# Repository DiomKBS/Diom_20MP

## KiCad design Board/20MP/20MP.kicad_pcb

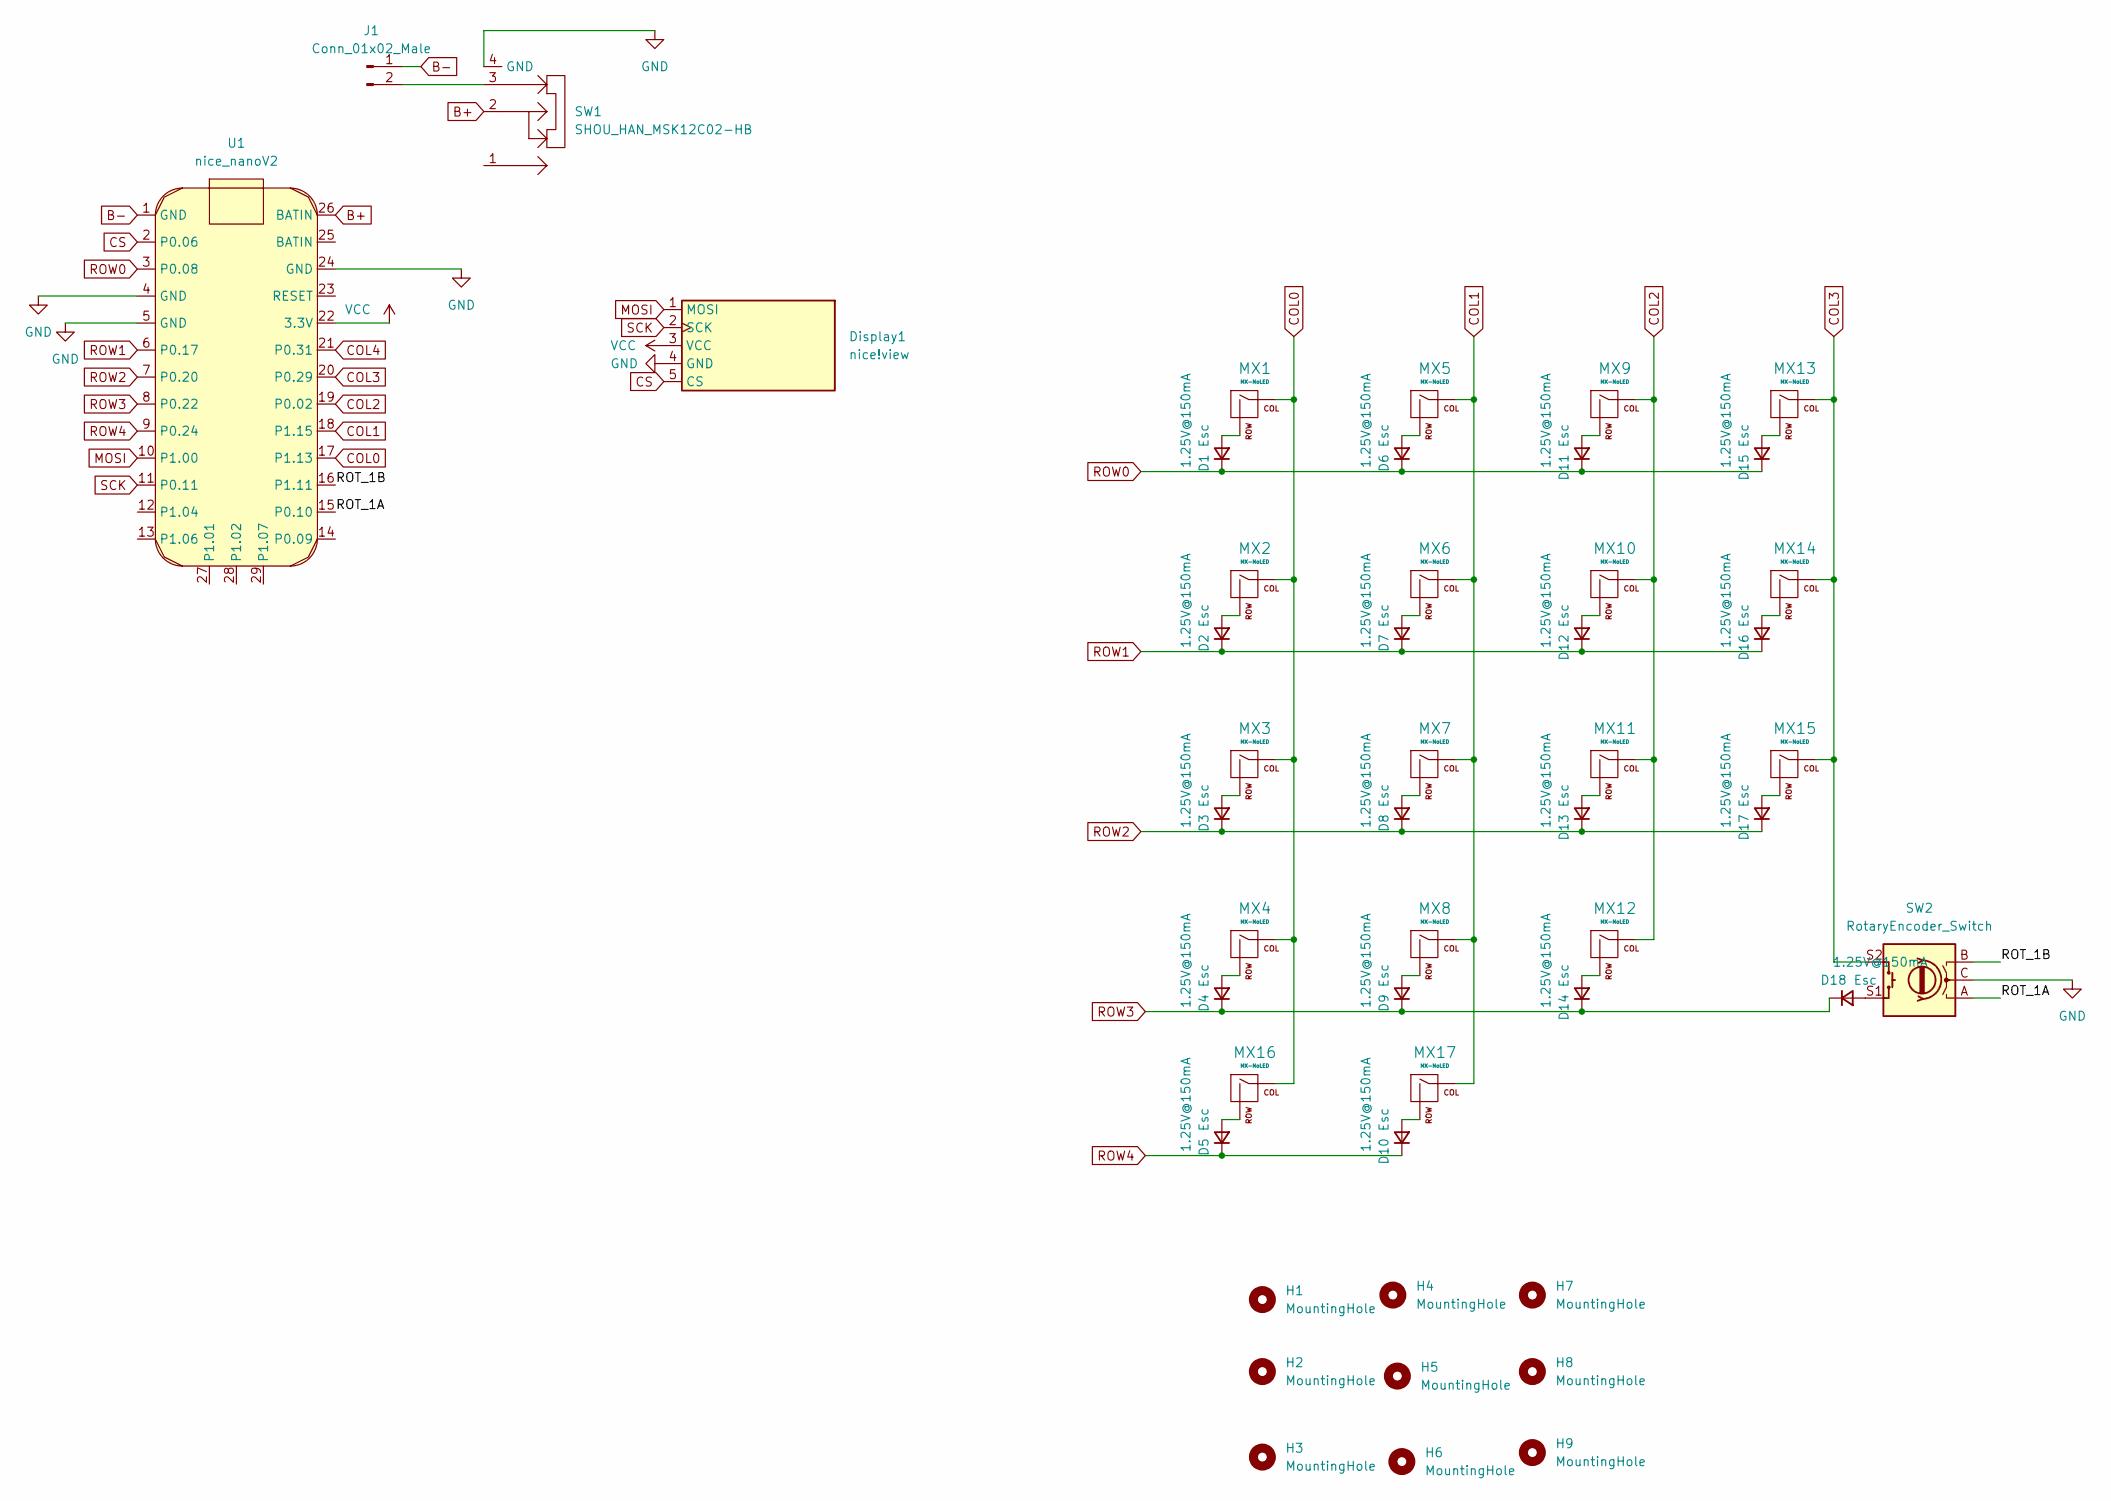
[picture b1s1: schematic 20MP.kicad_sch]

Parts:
D1, D2, D3, D4, D5, D6, D7, D8, D9, D10, D11, D12, D13, D14, D15, D16, D17, D18: 1.25V@150mA; D_SOD-123
Display1: nice!view; nice_view
H1, H2, H3, H4, H5, H6, H7, H8, H9: MountingHole; MountingHole_2.2mm_M2
J1: Conn_01x02_Male; THT_Battery
MX1, MX2, MX3, MX4, MX5, MX6, MX7, MX8, MX9, MX10, MX11, MX12, MX13, MX17: MX-NoLED; CherryMX-1.00U
MX14, MX15: MX-NoLED; CherryMX-2.00U_90deg
MX16: MX-NoLED; CherryMX-2.00U
SW1: SHOU_HAN_MSK12C02-HB; SHOU HAN MSK12C02-HB
SW2: RotaryEncoder_Switch; RotaryEncoder_EC11E-Switch
U1: nice_nanoV2

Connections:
/ROT_1A: SW2.A, U1.15 (P0.10)
/ROT_1B: SW2.B, U1.16 (P1.11)
B+: SW1.2, U1.26 (BATIN)
B-: J1.1, U1.1 (GND)
COL0: MX1.1 (COL), MX2.1 (COL), MX3.1 (COL), MX4.1 (COL), MX16.1 (COL), U1.17 (P1.13)
COL1: MX5.1 (COL), MX6.1 (COL), MX7.1 (COL), MX8.1 (COL), MX17.1 (COL), U1.18 (P1.15)
COL4: U1.21 (P0.31)
CS: Display1.5 (CS), U1.2 (P0.06)
GND: Display1.4 (GND), SW1.4 (GND), SW2.C, U1.4 (GND), U1.5 (GND), U1.24 (GND)
MOSI: Display1.1 (MOSI), U1.10 (P1.00)
unnamed: D1.2 (A), MX1.2 (ROW)
unnamed: D2.2 (A), MX2.2 (ROW)
unnamed: D3.2 (A), MX3.2 (ROW)
unnamed: D4.2 (A), MX4.2 (ROW)
unnamed: D5.2 (A), MX16.2 (ROW)
unnamed: D6.2 (A), MX5.2 (ROW)
unnamed: D7.2 (A), MX6.2 (ROW)
unnamed: D8.2 (A), MX7.2 (ROW)
unnamed: D9.2 (A), MX8.2 (ROW)
unnamed: D10.2 (A), MX17.2 (ROW)
unnamed: D11.2 (A), MX9.2 (ROW)
unnamed: D12.2 (A), MX10.2 (ROW)
unnamed: D13.2 (A), MX11.2 (ROW)
unnamed: D14.2 (A), MX12.2 (ROW)
unnamed: D15.2 (A), MX13.2 (ROW)
unnamed: D16.2 (A), MX14.2 (ROW)
unnamed: D17.2 (A), MX15.2 (ROW)
unnamed: D18.2 (A), SW2.S1
unnamed: J1.2, SW1.3
ROW0: D1.1 (K), D6.1 (K), D11.1 (K), D15.1 (K), U1.3 (P0.08)
ROW1: D2.1 (K), D7.1 (K), D12.1 (K), D16.1 (K), U1.6 (P0.17)
ROW2: D3.1 (K), D8.1 (K), D13.1 (K), D17.1 (K), U1.7 (P0.20)
ROW3: D4.1 (K), D9.1 (K), D14.1 (K), D18.1 (K), U1.8 (P0.22)
ROW4: D5.1 (K), D10.1 (K), U1.9 (P0.24)
SCK: Display1.2 (SCK), U1.11 (P0.11)
VCC: Display1.3 (VCC), U1.22 (3.3V)

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
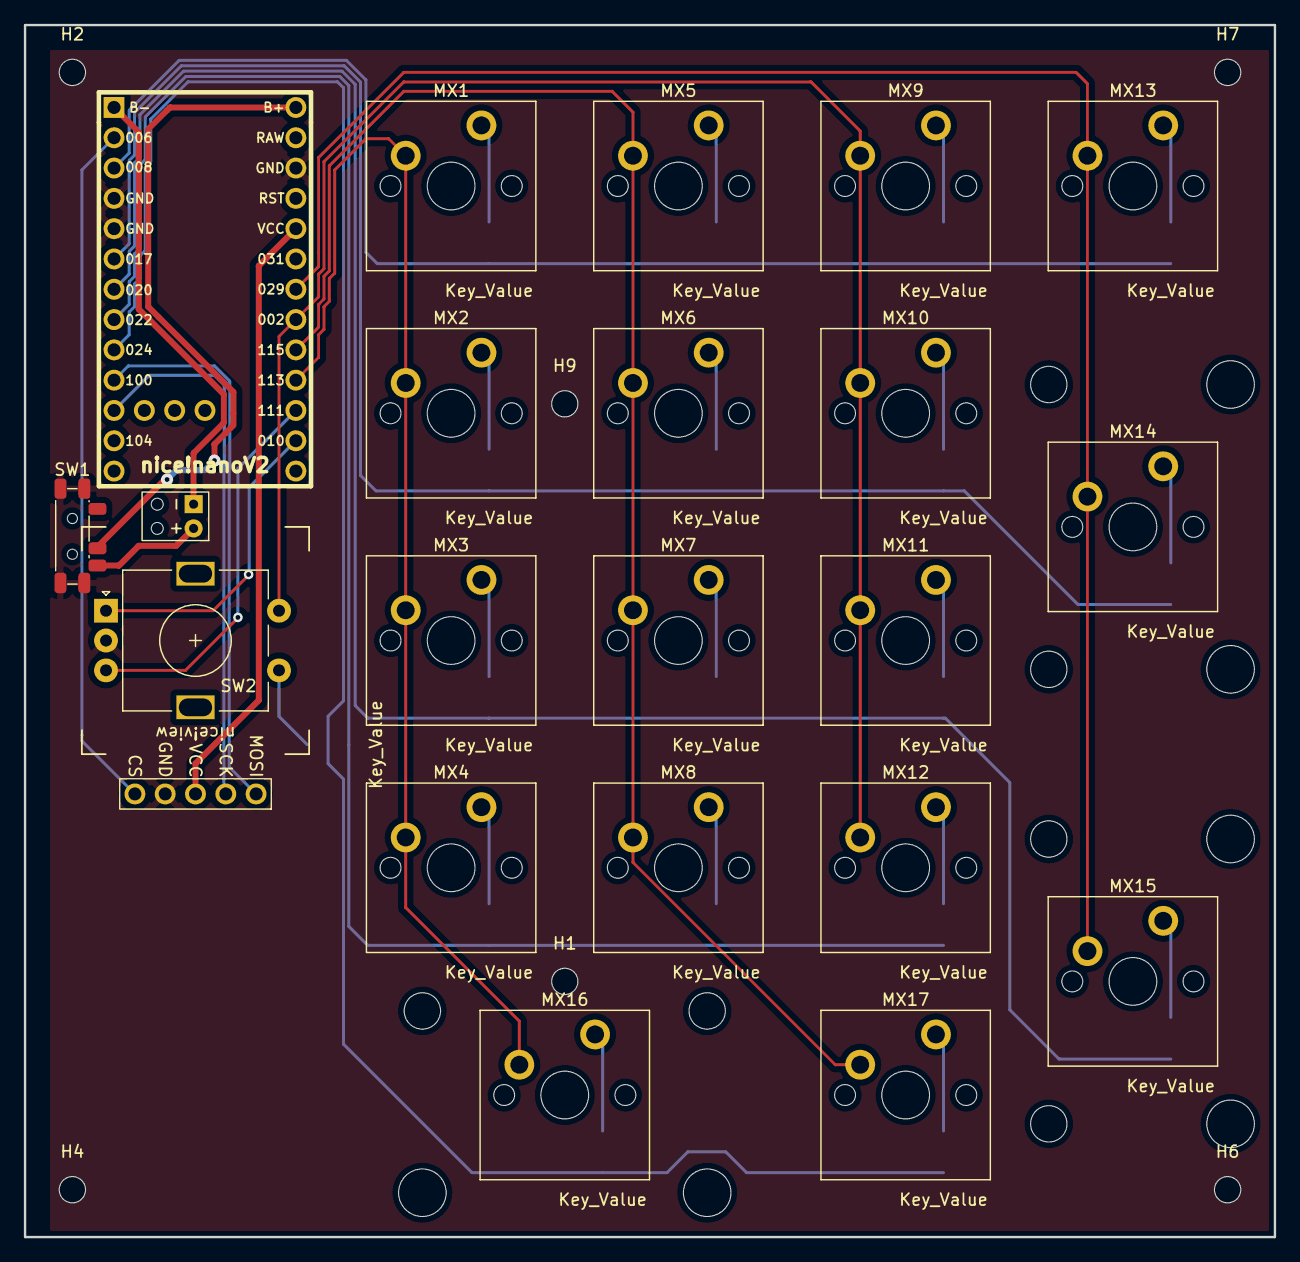
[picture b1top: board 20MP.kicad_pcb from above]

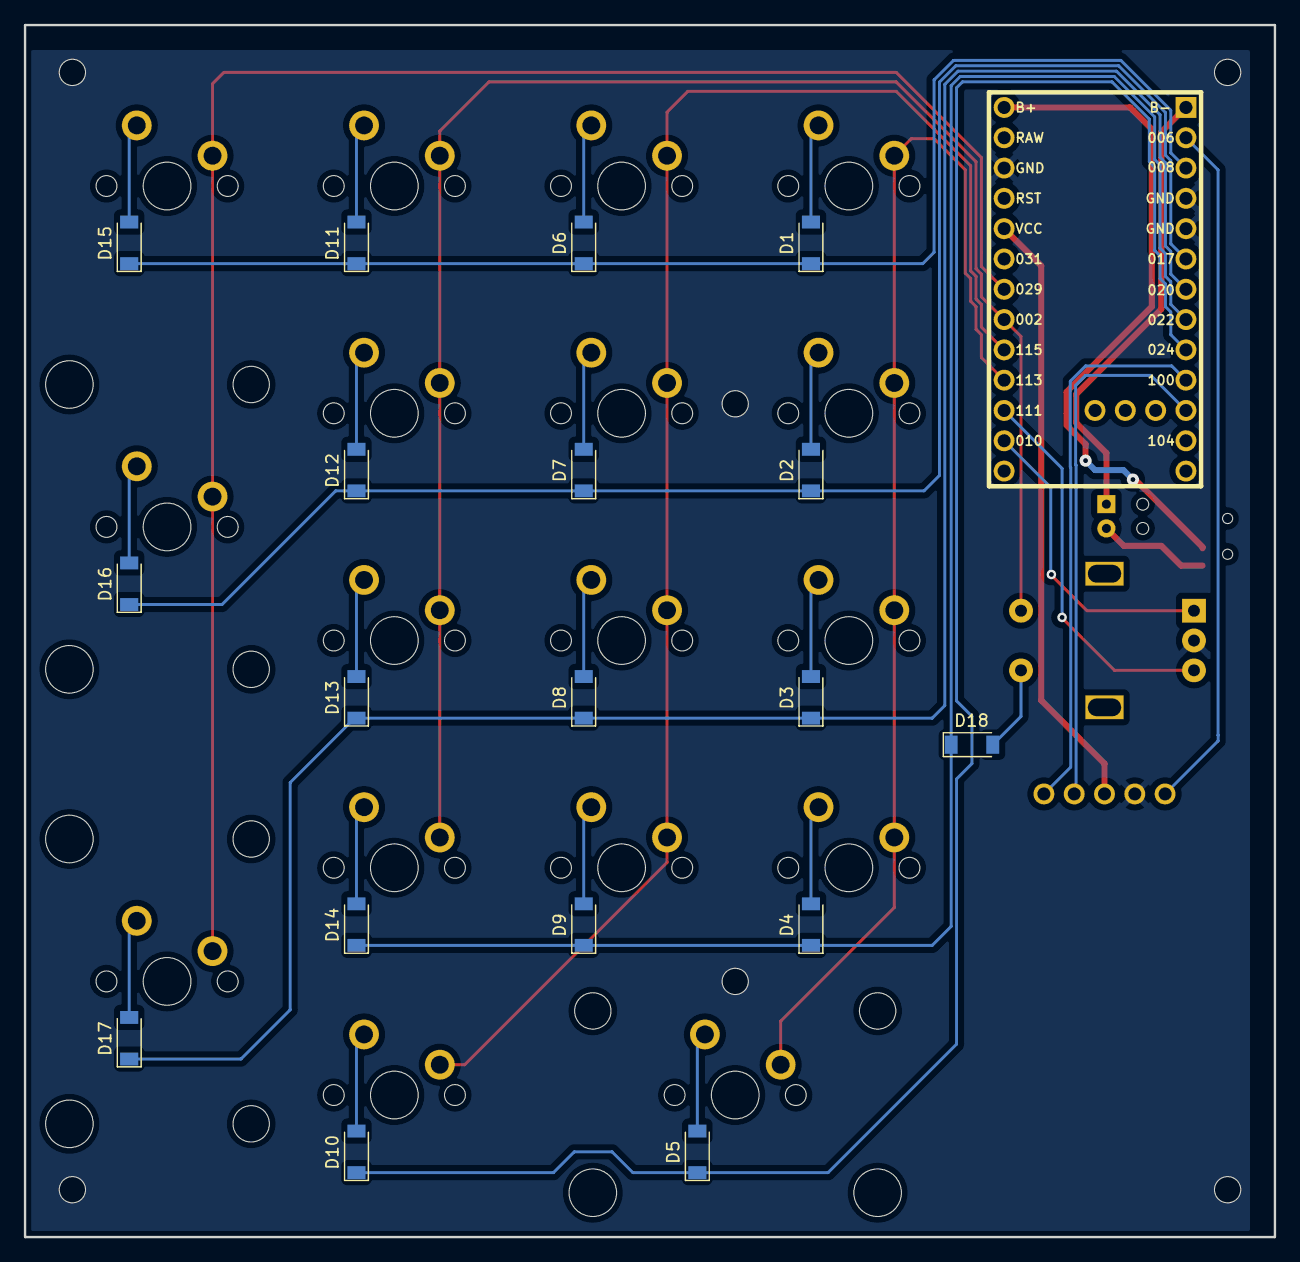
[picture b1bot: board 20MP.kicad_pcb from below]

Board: 2 copper layers, 104.8 x 101.6 mm, 49 parts (18 on the bottom side), 37 nets.

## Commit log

2023-05-28 init]
2023-06-01 Finished Schematic and assigned Footprints
2023-08-20 removed led's
2023-08-21 removed LED's and added first librarys
2023-08-22 added nice_nanoV2
2023-08-22 PCB basic layout
2023-08-22 update shematic
2023-08-28 added nice view to shematic
2023-09-14 removed old tracks
2023-09-14 added nice view
2023-09-14 changed diodes to smd
2023-09-14 added matrix traces
2023-09-14 added power
2023-09-14 changed oled wiring
2023-09-14 wired oled on pcb
2023-09-14 finished pcb
2023-09-19 bump kicad to 7.0.7
